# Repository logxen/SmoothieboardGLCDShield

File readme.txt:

Smoothieboard GLCD Shield

Licensed under the CERN Open Hardware License version 1.2

This simple pcb makes connecting the common Reprap Discount GLCD Screen to a Smoothieboard very easy. It has an optional footprint for a 5V regulator to make sure the screen gets enough power. Information on how to configure Smoothieware for use with a display panel can be found here: http://smoothieware.org/panel

The only truly required component other than the connectors is a schottky diode such as SK310A.

Bill of Materials:

2x SK310A (or similar) SMA schottky diodes to protect voltage inputs from reverse flow
2x 0.1uF 0603 capacitors
1x R78E5.0-0.5 switching voltage regulator
2x 2x5 0.1" shrouded male header
1x 1x3 0.1" male breakaway header
1x 0.1" jumper
2x 2x3 0.1" female header
2x 1x3 0.1" female header
1x 1x4 0.1" female header
1x 1x5 0.1" female header
1x 1x6 0.1" stacking female header (or just a 1x3 female header)

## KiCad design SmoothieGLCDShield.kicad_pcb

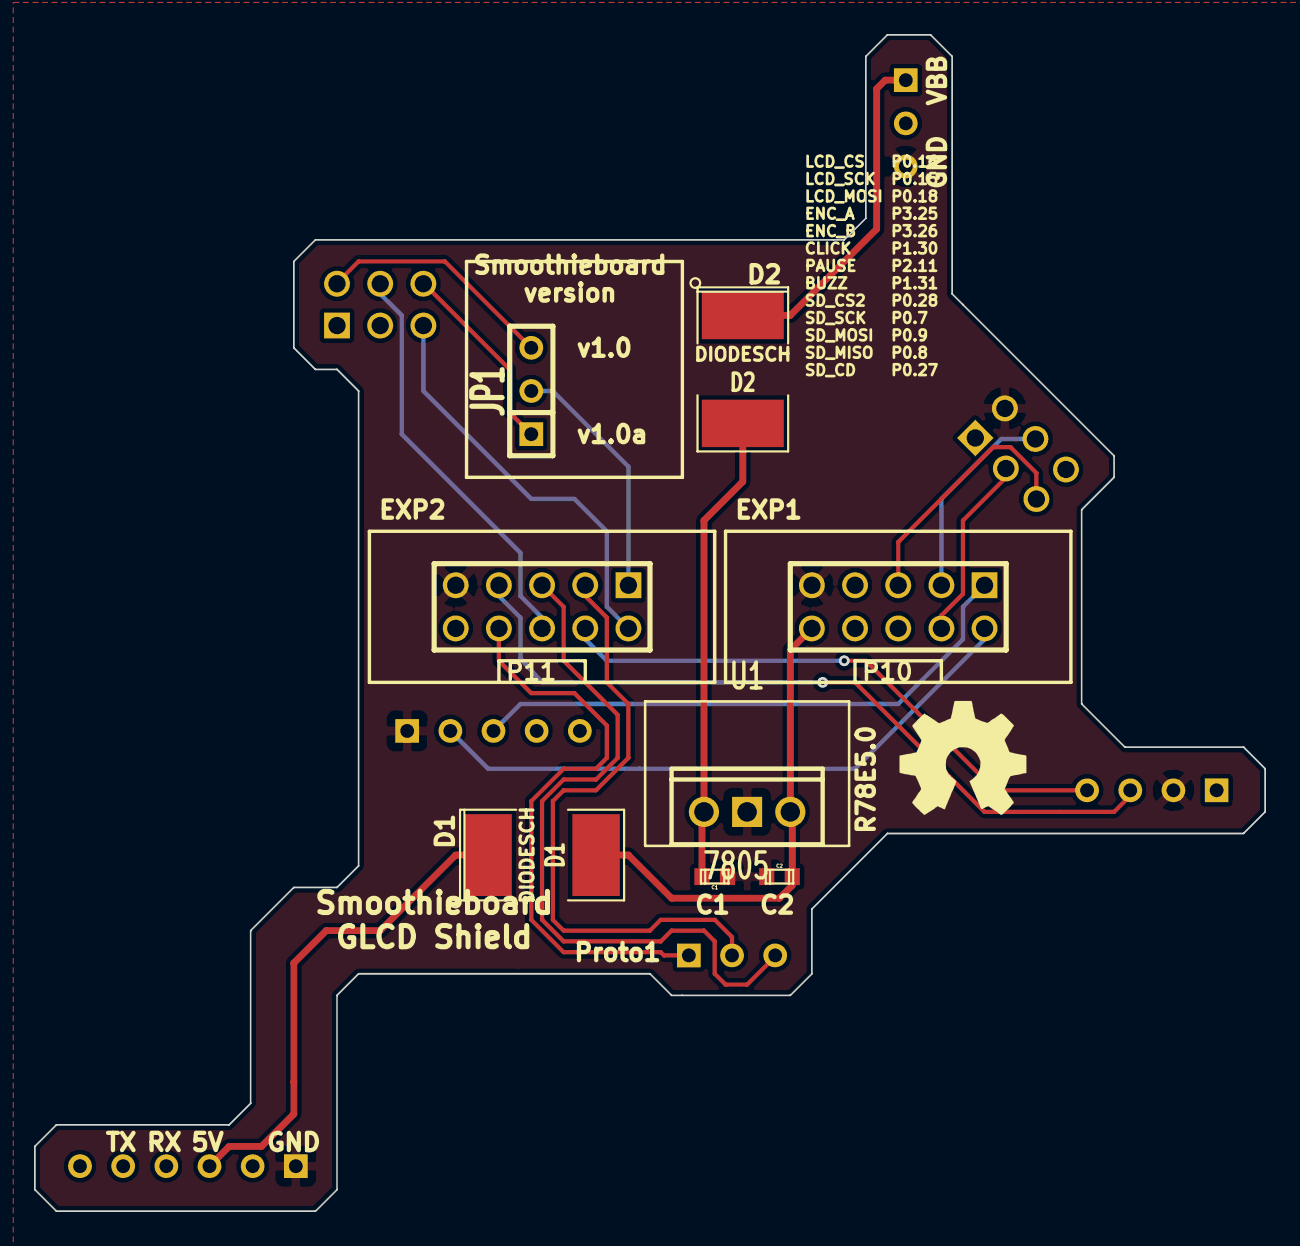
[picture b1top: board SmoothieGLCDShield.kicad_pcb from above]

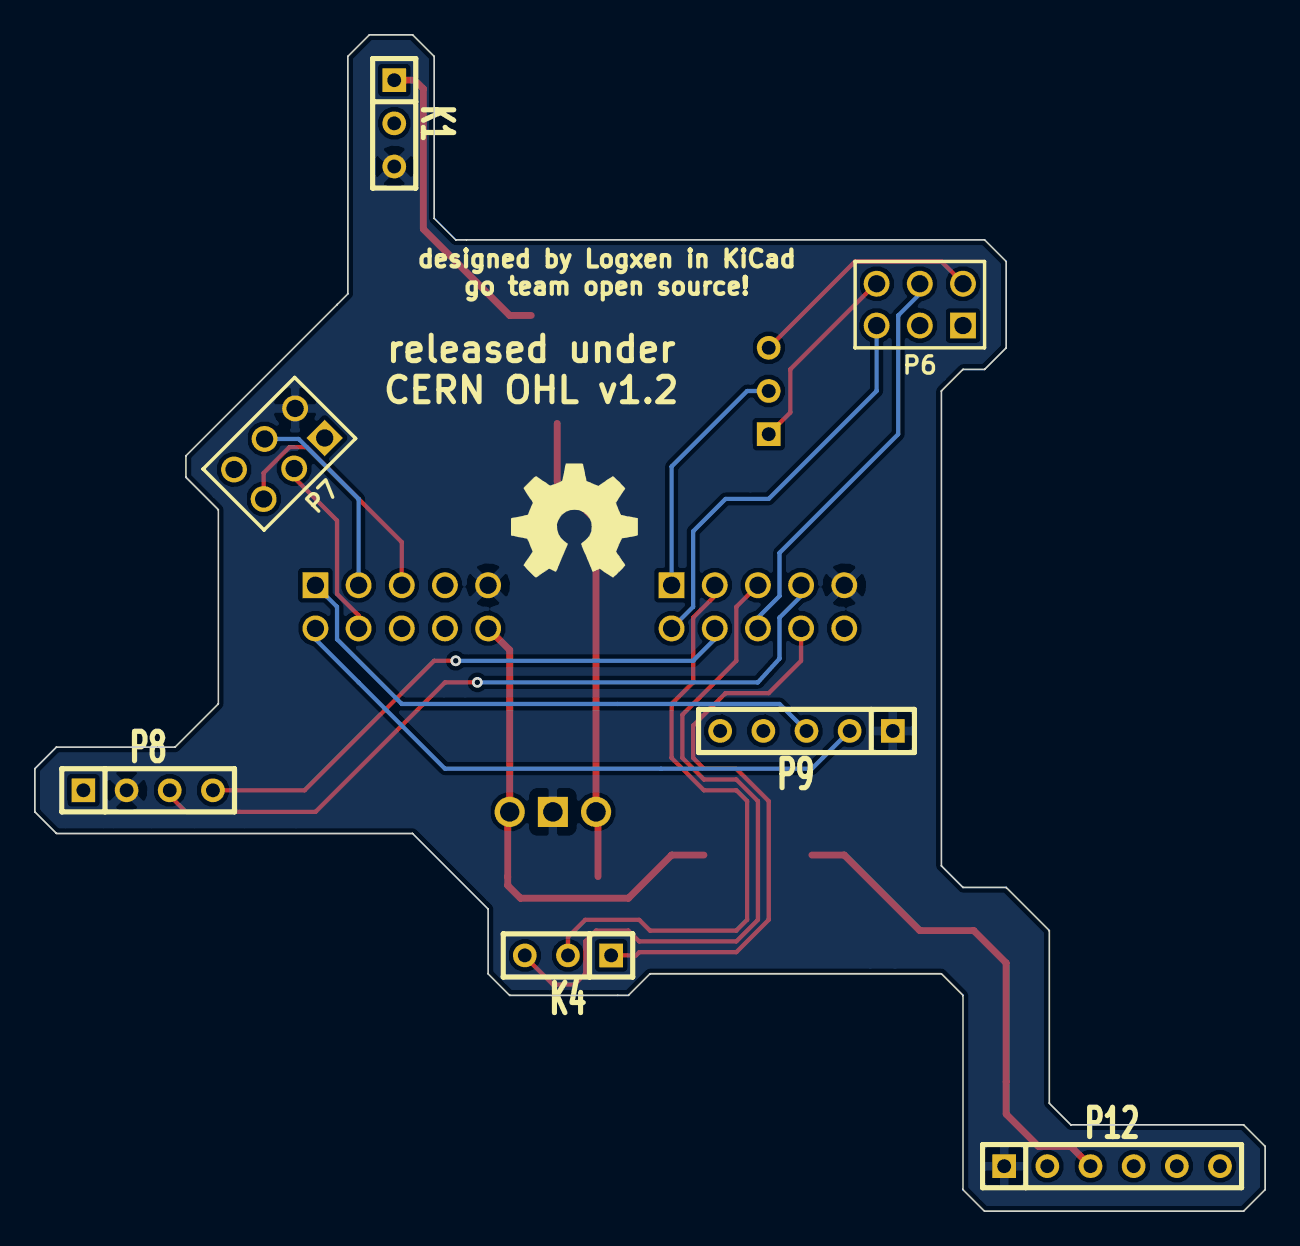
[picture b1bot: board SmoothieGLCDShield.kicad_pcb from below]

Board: 2 copper layers, 72.4 x 69.2 mm, 17 parts (8 on the bottom side), 20 nets.

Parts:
C1, C2: C; c_0603
D1, D2: DIODESCH; SM2112L
JP1: JUMPER3; SIL-3
K1, K4: CONN_3; SIL-3
P6, P7: CONN_3X2; pin_array_3x2_pin1_REV
P8: CONN_4; SIL-4
P9: CONN_5; SIL-5
P10, P11: CONN_5X2; PIN_ARRAY_5x2
P12: CONN_6; SIL-6
U1: 7805; R-78E05
VAL: REF; OSHW-LOGO_SMALL
VAL#2: REF; OSHW-LOGO_SMALL

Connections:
/5V: C2.1, D1.2, P10.10, U1.VO
/5VIN: D1.1, P12.3
/GND: C1.2, C2.2, K1.3, P7.2, P8.2, P9.1, P10.9, P11.9, P12.1, U1.GND
/LCD_MOSI: P7.4, P10.3
/LCD_SCK: P7.5, P10.5
/LCD_SSEL: P7.3, P10.4
/P1.30: P9.2, P10.2
/P1.31: P9.3, P10.1
/P2.11: K4.1, P11.8
/P3.25: K4.3, P11.5
/P3.26: K4.2, P11.3
/SD_CD: P8.3, P11.7
/SD_MISO: JP1.2, P11.1
/SD_MISO_NEW: JP1.1, P6.6
/SD_MISO_OLD: JP1.3, P6.2
/SD_MOSI: P6.4, P11.6
/SD_SCK: P6.5, P11.2
/SD_SSEL2: P8.4, P11.4
/VBB: D2.1, K1.1
/VBB_REG: C1.1, D2.2, U1.VI

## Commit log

2014-12-13 :space_invader: Added .gitattributes & .gitignore files
2014-12-13 Prototype 1
    Initial commit of Proto1 design

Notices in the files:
SmoothieGLCDShield.kicad_pcb:
released under
CERN OHL v1.2
